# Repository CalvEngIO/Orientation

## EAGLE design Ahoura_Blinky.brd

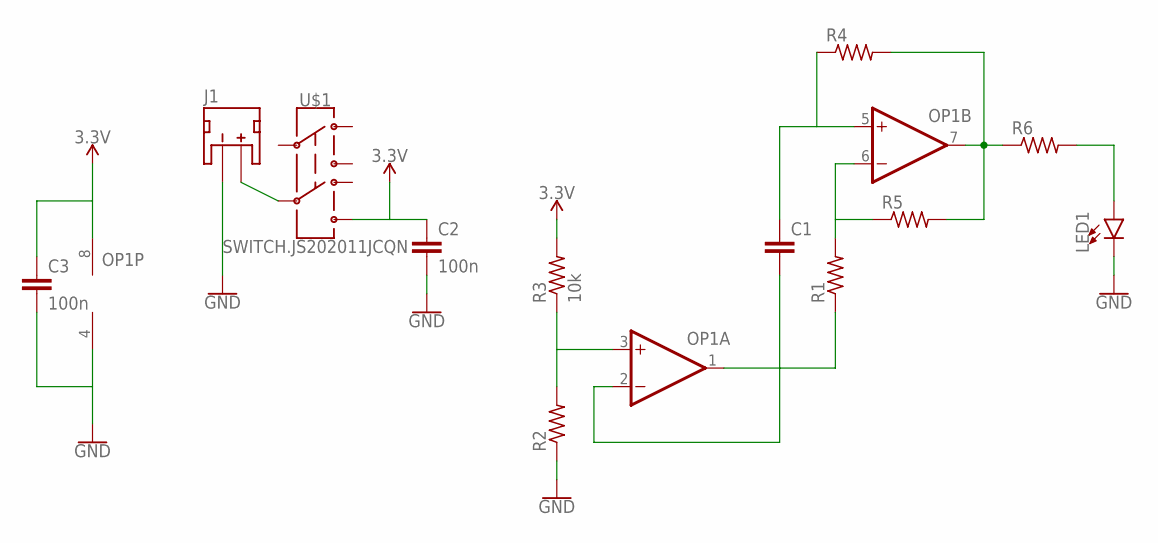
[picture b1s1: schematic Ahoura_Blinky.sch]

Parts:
C1: CAPACITOR0402; C0402
C2, C3: 100n; C0402
J1: JST_2MM_MALE; JST-2-SMD
LED1: LED0603; LED-0603
OP1: OP-DUALRM; MSOP08
R1, R2, R4, R5, R6: RESISTOR0402; R0402
R3: 10k; R0402
U$1: SWITCH.JS202011JCQN; SWITCH.00

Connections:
3.3V: C2.1, C3.1, OP1.8 (V+), R3.2, U$1.7
GND: C2.2, C3.2, J1.1 (-), LED1.C, OP1.4 (V-), R2.1
unnamed: J1.2 (+), U$1.6
unnamed: OP1.7 (OUT), R4.2, R5.2, R6.1
unnamed: OP1.3 (+IN), R2.2, R3.1
unnamed: C1.2, OP1.1 (OUT), OP1.2 (-IN), R1.1
unnamed: C1.1, OP1.5 (+IN), R4.1
unnamed: OP1.6 (-IN), R1.2, R5.1
unnamed: LED1.A, R6.2

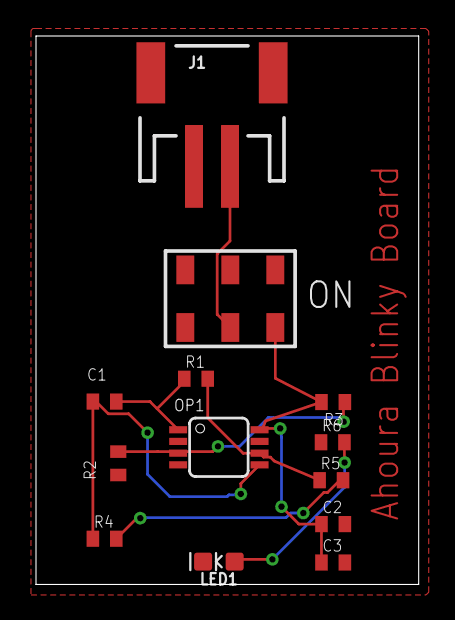
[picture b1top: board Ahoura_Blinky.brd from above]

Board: 2 copper layers, 21.3 x 30.5 mm, 13 parts (0 on the bottom side), 9 nets.

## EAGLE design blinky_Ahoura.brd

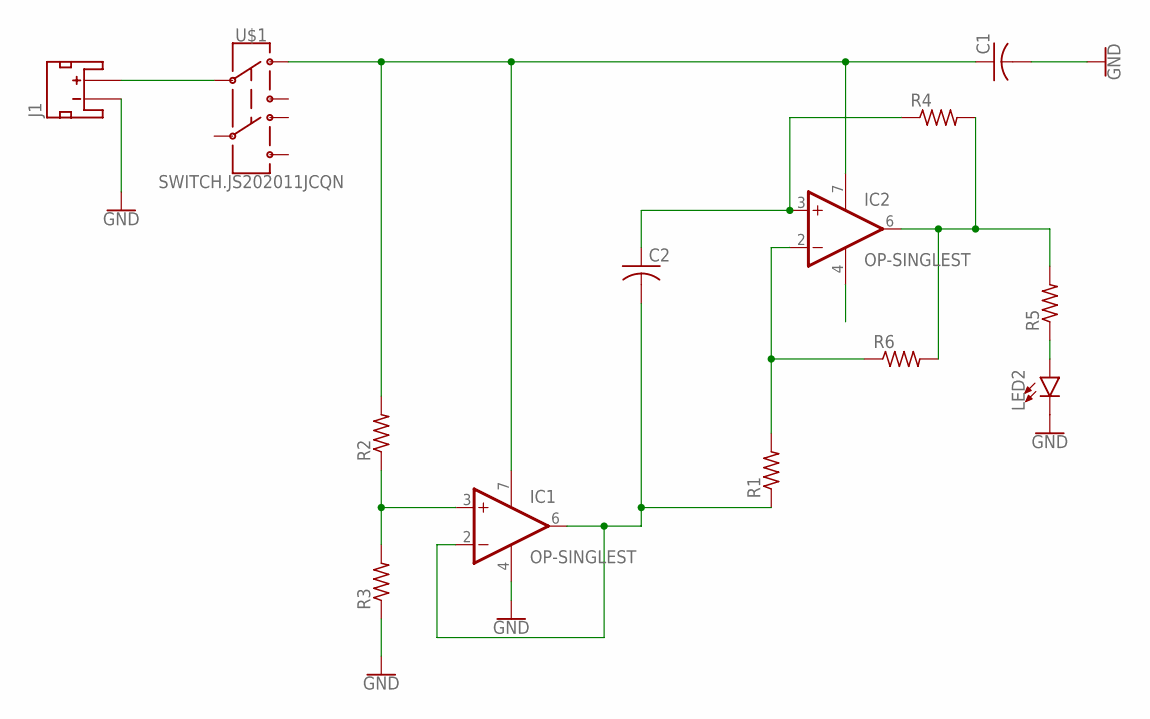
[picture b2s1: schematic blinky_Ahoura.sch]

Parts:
C1, C2: C-USC0402; C0402
IC1, IC2: OP-SINGLEST; TSSOP8
J1: JST_2MM_MALE; JST-2-SMD
LED2: LED0603; LED-0603
R1, R2, R3, R4, R5, R6: R-US_R0402; R0402
U$1: SWITCH.JS202011JCQN; SWITCH.00

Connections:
GND: C1.2, IC1.4 (V-), J1.1 (-), LED2.C, R3.1
unnamed: J1.2 (+), U$1.2
unnamed: LED2.A, R5.1
unnamed: C1.1, IC1.7 (V+), IC2.7 (V+), R2.2, U$1.1
unnamed: IC1.3 (+IN), R2.1, R3.2
unnamed: C2.2, IC1.2 (-IN), IC1.6 (OUT), R1.1
unnamed: C2.1, IC2.3 (+IN), R4.1
unnamed: IC2.6 (OUT), R4.2, R5.2, R6.2
unnamed: IC2.2 (-IN), R1.2, R6.1

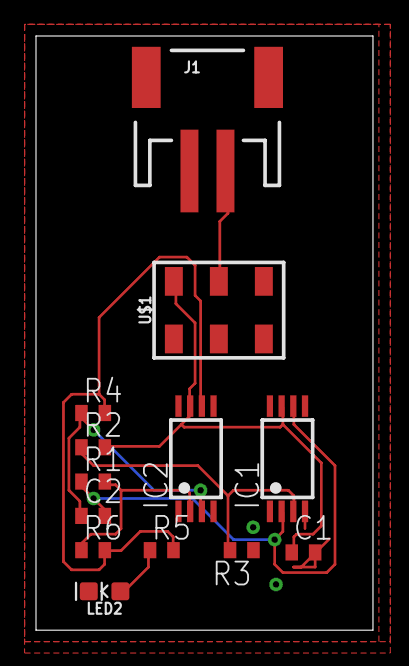
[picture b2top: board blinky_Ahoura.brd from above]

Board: 2 copper layers, 18.7 x 33.0 mm, 13 parts (0 on the bottom side), 9 nets.

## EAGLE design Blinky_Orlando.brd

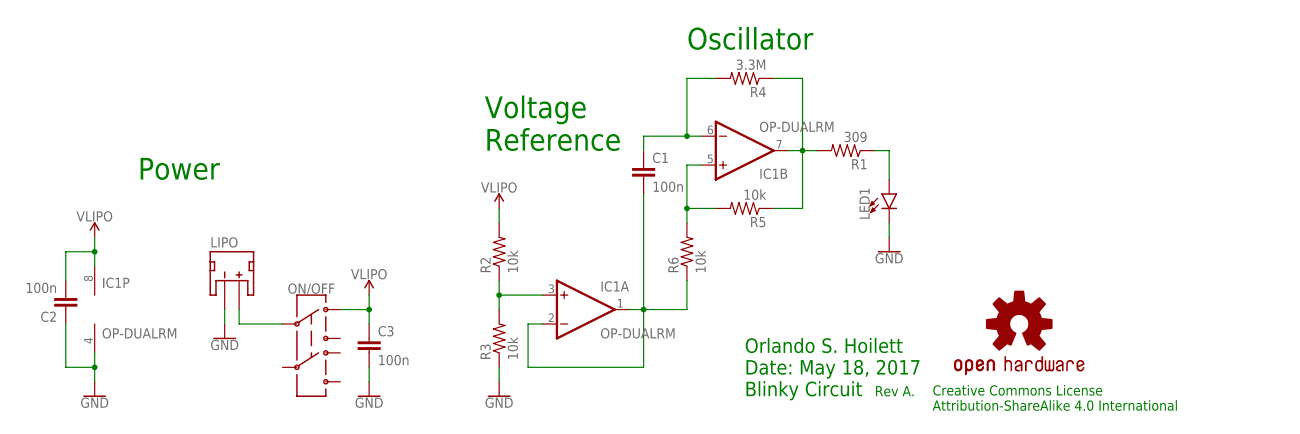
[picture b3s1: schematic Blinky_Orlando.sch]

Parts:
C1, C2, C3: 100n; C0402
IC1: OP-DUALRM; MSOP08
LED1: LED0603; LED-0603
LIPO: JST_2MM_MALE; JST-2-SMD
LOGO1: OSHW-LOGOS; OSHW-LOGO-S
ON/OFF: SWITCH.JS202011JCQN; SWITCH.00
R1: 309; R0402
R2, R3, R5, R6: 10k; R0402
R4: 3.3M; R0402
U$4: CALVENGIO_HANDLEHANDLE.05; CALVENGIO_HANDLE.05

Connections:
GND: C2.1, C3.2, IC1.4 (V-), LED1.C, LIPO.1 (-), R3.1
unnamed: C1.1, IC1.6 (-IN), R4.2
unnamed: IC1.7 (OUT), R1.2, R4.1, R5.1
unnamed: LIPO.2 (+), ON/OFF.2
unnamed: IC1.5 (+IN), R5.2, R6.2
unnamed: C1.2, IC1.1 (OUT), IC1.2 (-IN), R6.1
unnamed: IC1.3 (+IN), R2.1, R3.2
unnamed: LED1.A, R1.1
VLIPO: C2.2, C3.1, IC1.8 (V+), ON/OFF.1, R2.2

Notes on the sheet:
Orlando S. Hoilett Date: May 18, 2017 Blinky Circuit
Rev A.
Creative Commons License Attribution-ShareAlike 4.0 International
Power
Oscillator
Voltage Reference

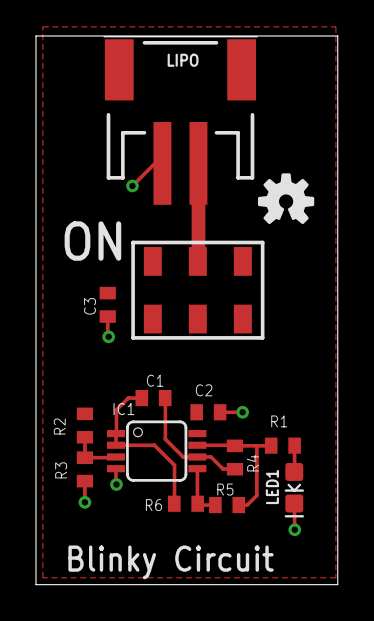
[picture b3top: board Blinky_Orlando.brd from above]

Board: 2 copper layers, 16.8 x 30.5 mm, 15 parts (1 on the bottom side), 9 nets.

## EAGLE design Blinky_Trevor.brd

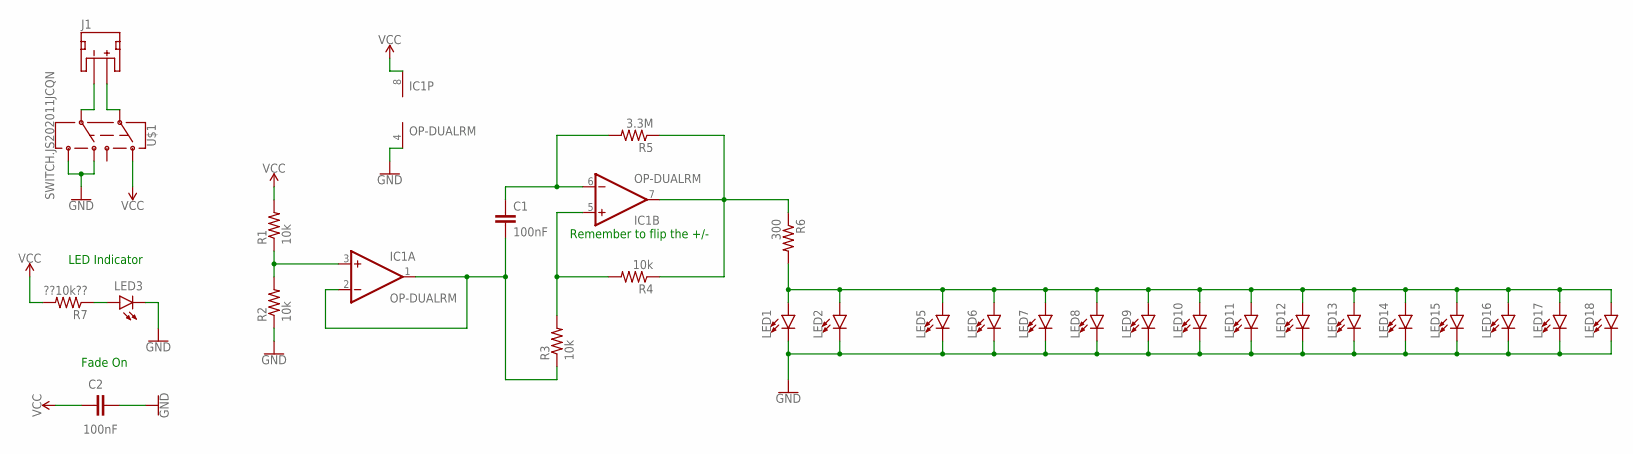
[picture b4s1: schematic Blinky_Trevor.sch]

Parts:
C1, C2: 100nF; C0402
IC1: OP-DUALRM; MSOP08
J1: JST_2MM_MALE; JST-2-SMD
LED1, LED2, LED3, LED5, LED6, LED7, LED8, LED9, LED10, LED11, LED12, LED13, LED14, LED15, LED16, LED17, LED18: LED0603; LED-0603
R1, R2, R3, R4: 10k; R0402
R5: 3.3M; R0402
R6: 300; R0402
R7: ??10k??; R0402
U$1: SWITCH.JS202011JCQN; SWITCH.00

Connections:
GND: C2.2, IC1.4 (V-), LED1.C, LED2.C, LED3.C, LED5.C, LED6.C, LED7.C, LED8.C, LED9.C, LED10.C, LED11.C, LED12.C, LED13.C, LED14.C, LED15.C, LED16.C, LED17.C, LED18.C, R2.1, U$1.5, U$1.7
unnamed: C1.2, IC1.1 (OUT), IC1.2 (-IN), R3.1
unnamed: IC1.3 (+IN), R1.1, R2.2
unnamed: IC1.5 (+IN), R3.2, R4.2
unnamed: IC1.7 (OUT), R4.1, R5.1, R6.1
unnamed: C1.1, IC1.6 (-IN), R5.2
unnamed: LED1.A, LED2.A, LED5.A, LED6.A, LED7.A, LED8.A, LED9.A, LED10.A, LED11.A, LED12.A, LED13.A, LED14.A, LED15.A, LED16.A, LED17.A, LED18.A, R6.2
unnamed: J1.1 (-), U$1.6
unnamed: J1.2 (+), U$1.2
unnamed: LED3.A, R7.1
VCC: C2.1, IC1.8 (V+), R1.2, R7.2, U$1.1

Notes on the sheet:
LED Indicator
Fade On
Remember to flip the +/-

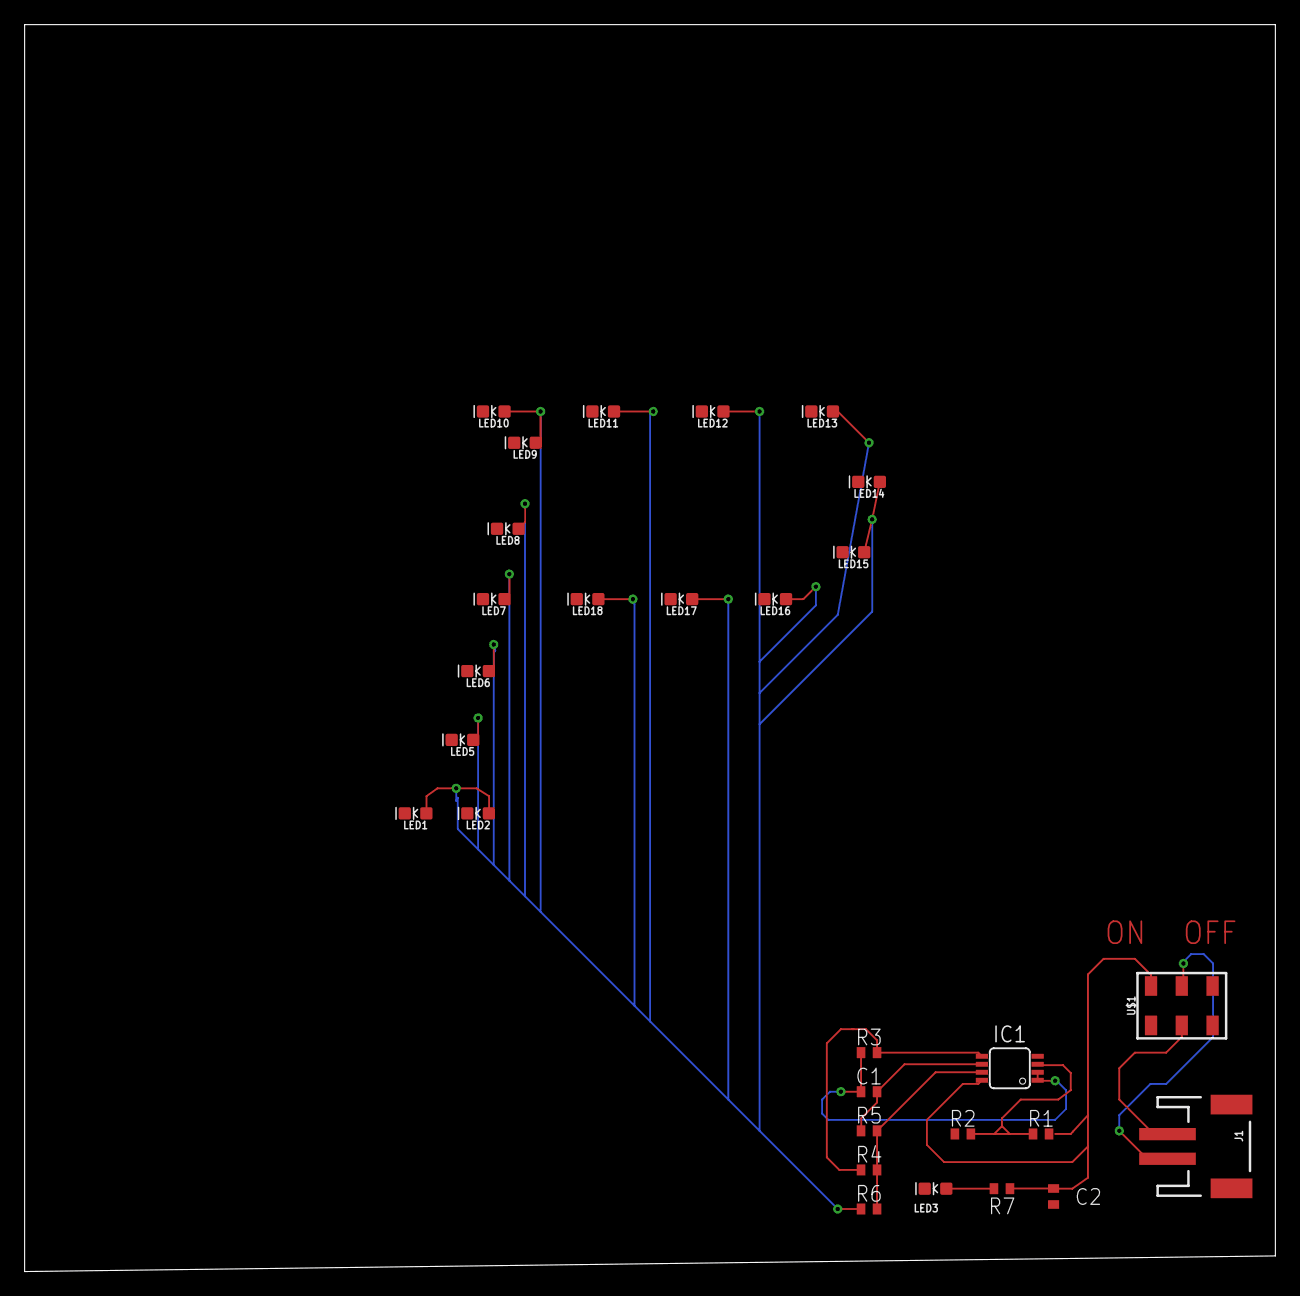
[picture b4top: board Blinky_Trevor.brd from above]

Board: 2 copper layers, 101.6 x 101.3 mm, 29 parts (0 on the bottom side), 11 nets.

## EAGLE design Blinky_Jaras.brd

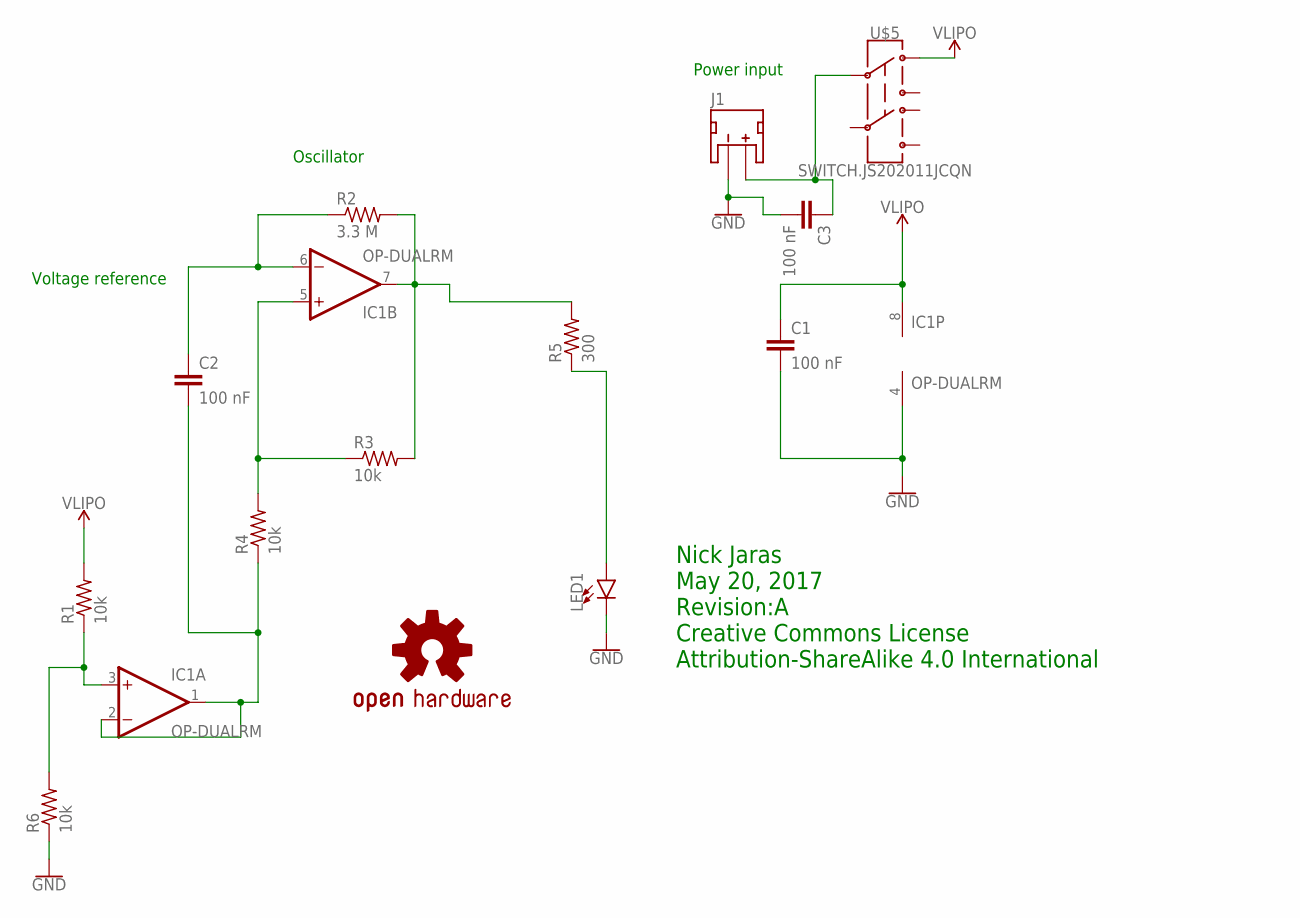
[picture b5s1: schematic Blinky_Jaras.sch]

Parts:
C1, C2, C3: 100 nF; C0402
IC1: OP-DUALRM; MSOP08
J1: JST_2MM_MALE; JST-2-SMD
LED1: LED0603; LED-0603
LOGO1: OSHW-LOGOS; OSHW-LOGO-S
R1, R3, R4, R6: 10k; R0402
R2: 3.3 M; R0402
R5: 300; R0402
U$4: CALVENGIO_HANDLEHANDLE.05; CALVENGIO_HANDLE.05
U$5: SWITCH.JS202011JCQN; SWITCH.00

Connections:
GND: C1.2, C3.2, IC1.4 (V-), J1.1 (-), LED1.C, R6.1
unnamed: C3.1, J1.2 (+), U$5.2
unnamed: IC1.5 (+IN), R3.1, R4.2
unnamed: IC1.7 (OUT), R2.2, R3.2, R5.2
unnamed: C2.1, IC1.6 (-IN), R2.1
unnamed: LED1.A, R5.1
unnamed: C2.2, IC1.1 (OUT), IC1.2 (-IN), R4.1
unnamed: IC1.3 (+IN), R1.1, R6.2
VLIPO: C1.1, IC1.8 (V+), R1.2, U$5.1

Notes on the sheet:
Nick Jaras May 20, 2017 Revision:A Creative Commons License Attribution-ShareAlike 4.0 International
Power input
Oscillator
Voltage reference

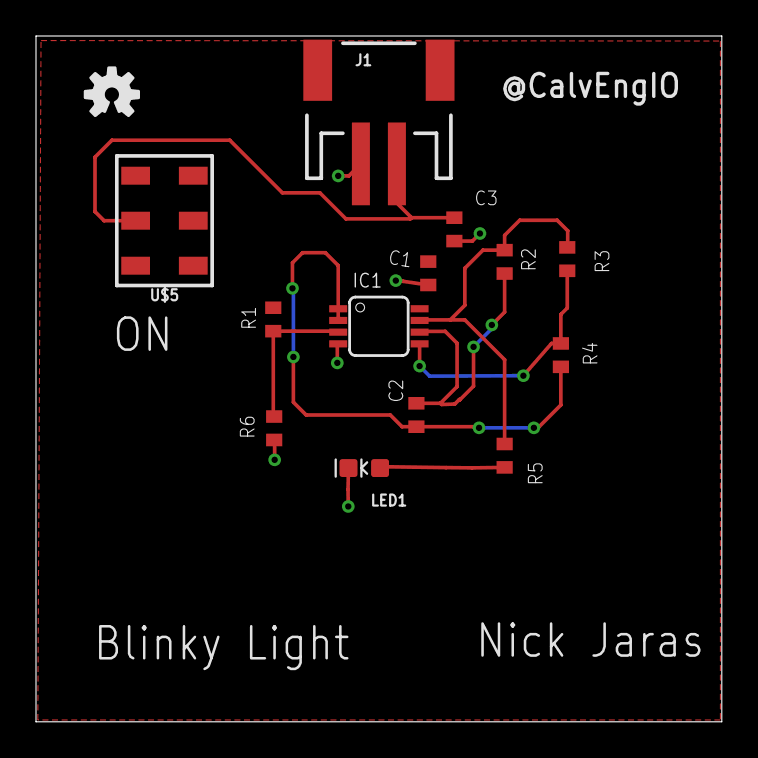
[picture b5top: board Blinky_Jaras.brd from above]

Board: 2 copper layers, 38.1 x 38.1 mm, 15 parts (0 on the bottom side), 9 nets.

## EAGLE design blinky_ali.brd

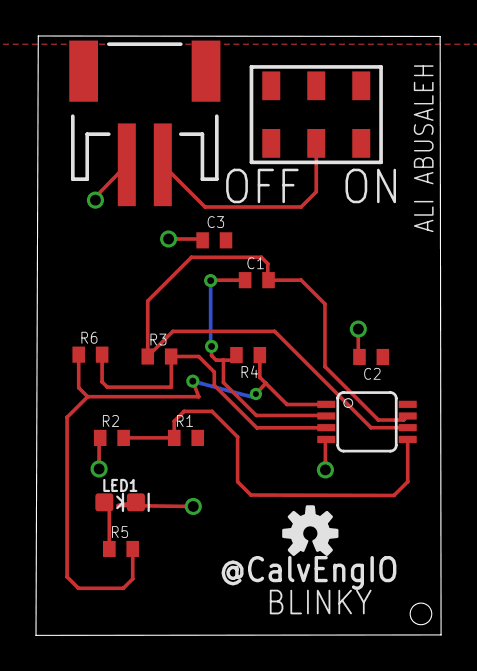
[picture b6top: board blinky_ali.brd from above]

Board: 2 copper layers, 22.5 x 33.3 mm, 15 parts (0 on the bottom side), 9 nets.

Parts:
C1, C2, C3: 100nF; C0402
IC1: OP-DUALRM; MSOP08
J1: JST-2-SMD
LED1: LED-0603
LOGO1: OSHW-LOGOS; OSHW-LOGO-S
R1, R2, R3, R6: 10K; R0402
R4: 3.3M; R0402
R5: 300; R0402
U$4: CALVENGIO_HANDLEHANDLE.05; CALVENGIO_HANDLE.05
U$5: SWITCH.JS202011JCQN; SWITCH.00

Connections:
GND: C2.2, C3.1, IC1.4, J1.1, LED1.C, R2.1
unnamed: C1.1, IC1.2, R4.2
unnamed: IC1.5, R1.1, R2.2
unnamed: C1.2, IC1.6, IC1.7, R3.1
unnamed: IC1.1, R4.1, R5.2, R6.1
unnamed: IC1.3, R3.2, R6.2
unnamed: J1.2, U$5.2
unnamed: LED1.A, R5.1
VLIPO: C2.1, C3.2, IC1.8, R1.2, U$5.1

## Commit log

2017-03-30 common GitHub commands
2017-04-05 Peyton's Text File
2017-04-05 File in Branch
2017-04-06 added a file with my name to my branch
2017-04-30 Orientation
2017-04-30 Added to wrong branch
2017-05-14 ALI ABUSALEH
2017-05-14 new file
2017-05-14 Create ali_myBranch
2017-05-17 Nick's Text File
2017-05-17 Removed mybranch in wrong place
2017-05-17 Adding file to my branch
2017-05-20 ali's board
2017-05-21 final design (changed the name placement)
2017-05-22 Blinky board board file
2017-05-27 made changes to Nick's board by moving the silkscreen of his name over just a test and added my board as a reference
2017-06-09 Added Trevor's Orientation File
2017-06-09 Added a change within a branch
2017-06-09 Add Trevor's Blink Circuit
2017-06-12 Added LED Pattern
2017-07-07 this is task 1
2017-09-02 blinky_Ahoura.brd
2017-09-08 test
2017-09-08 New updates
2017-09-22 changed size of text and smashed
2017-09-22 more updates
